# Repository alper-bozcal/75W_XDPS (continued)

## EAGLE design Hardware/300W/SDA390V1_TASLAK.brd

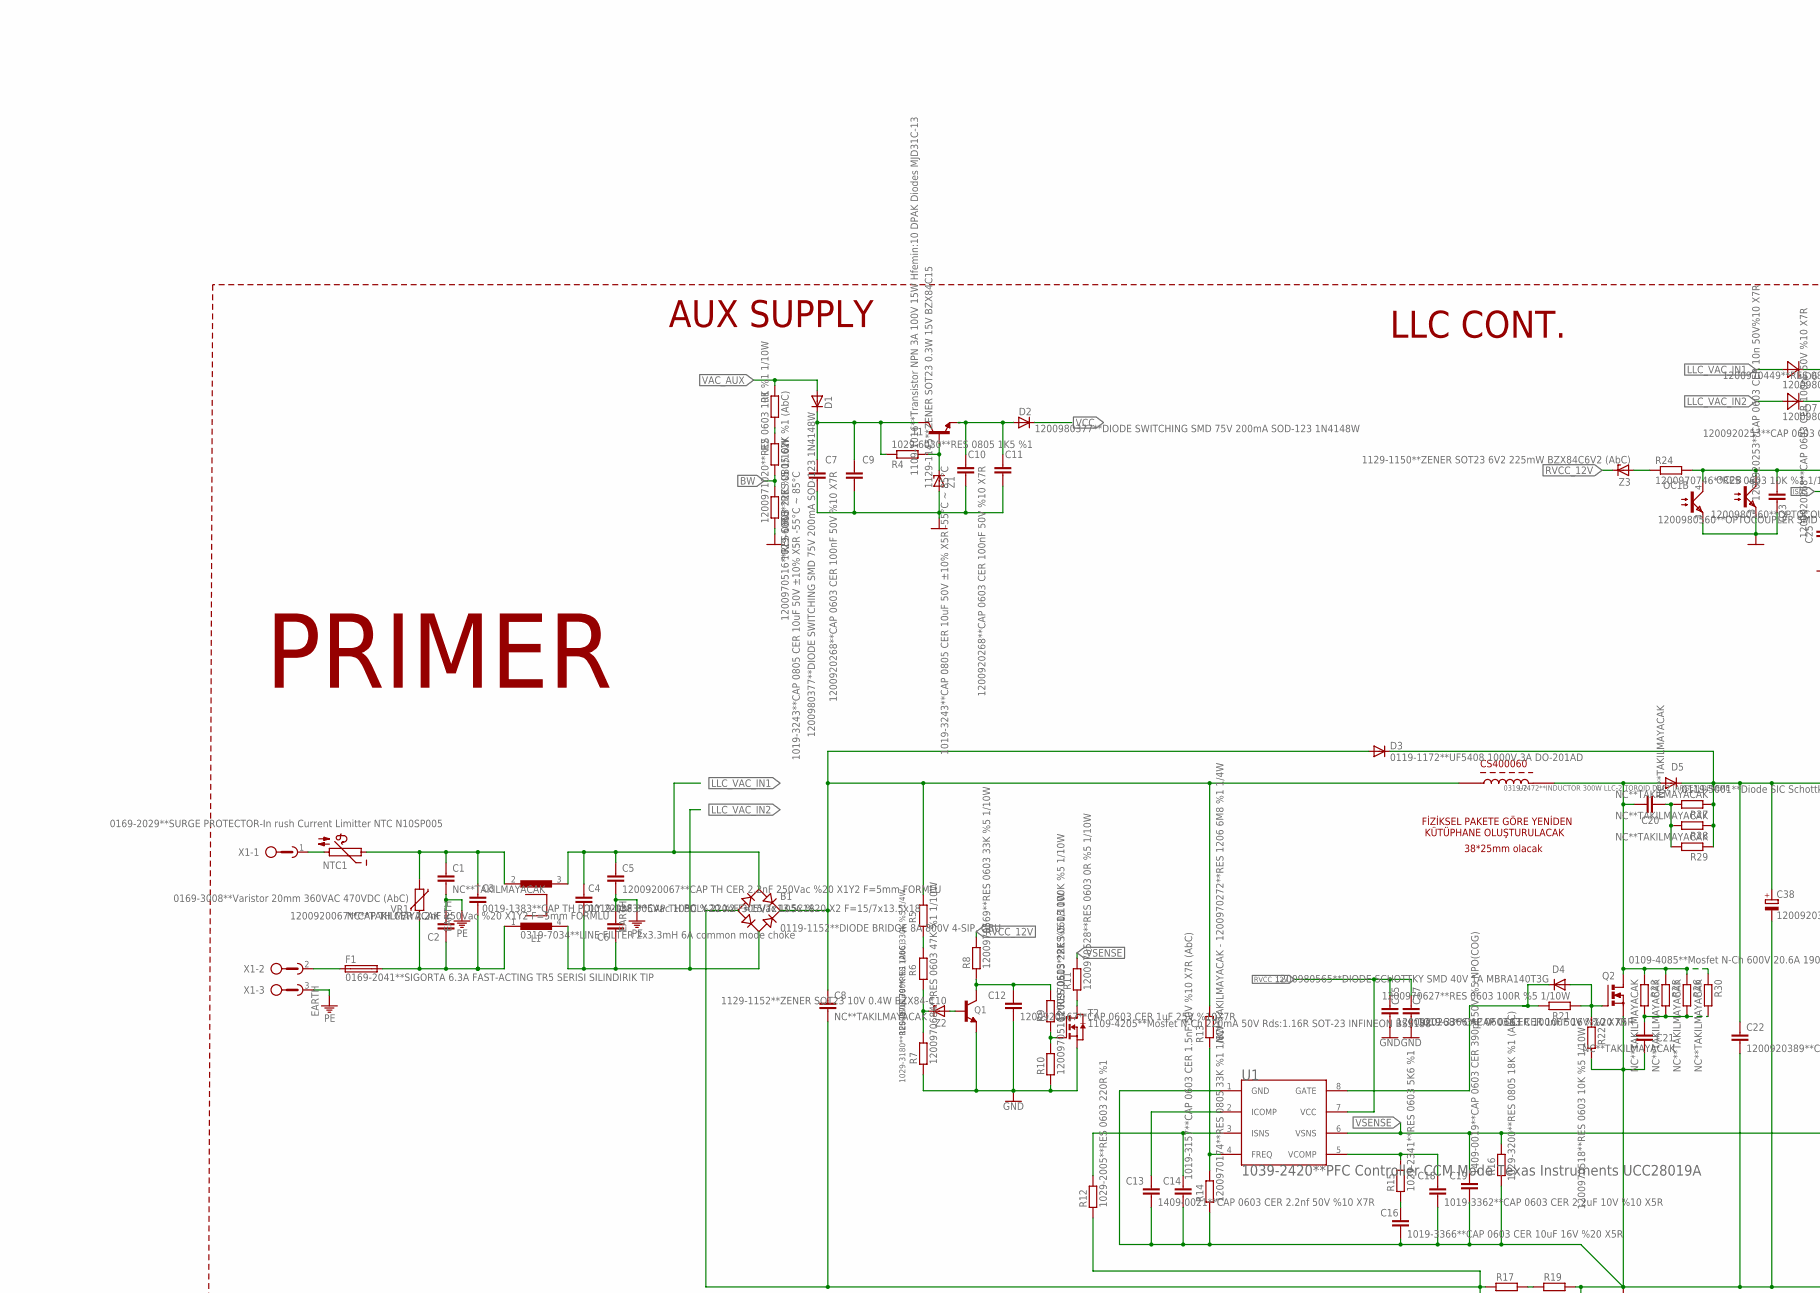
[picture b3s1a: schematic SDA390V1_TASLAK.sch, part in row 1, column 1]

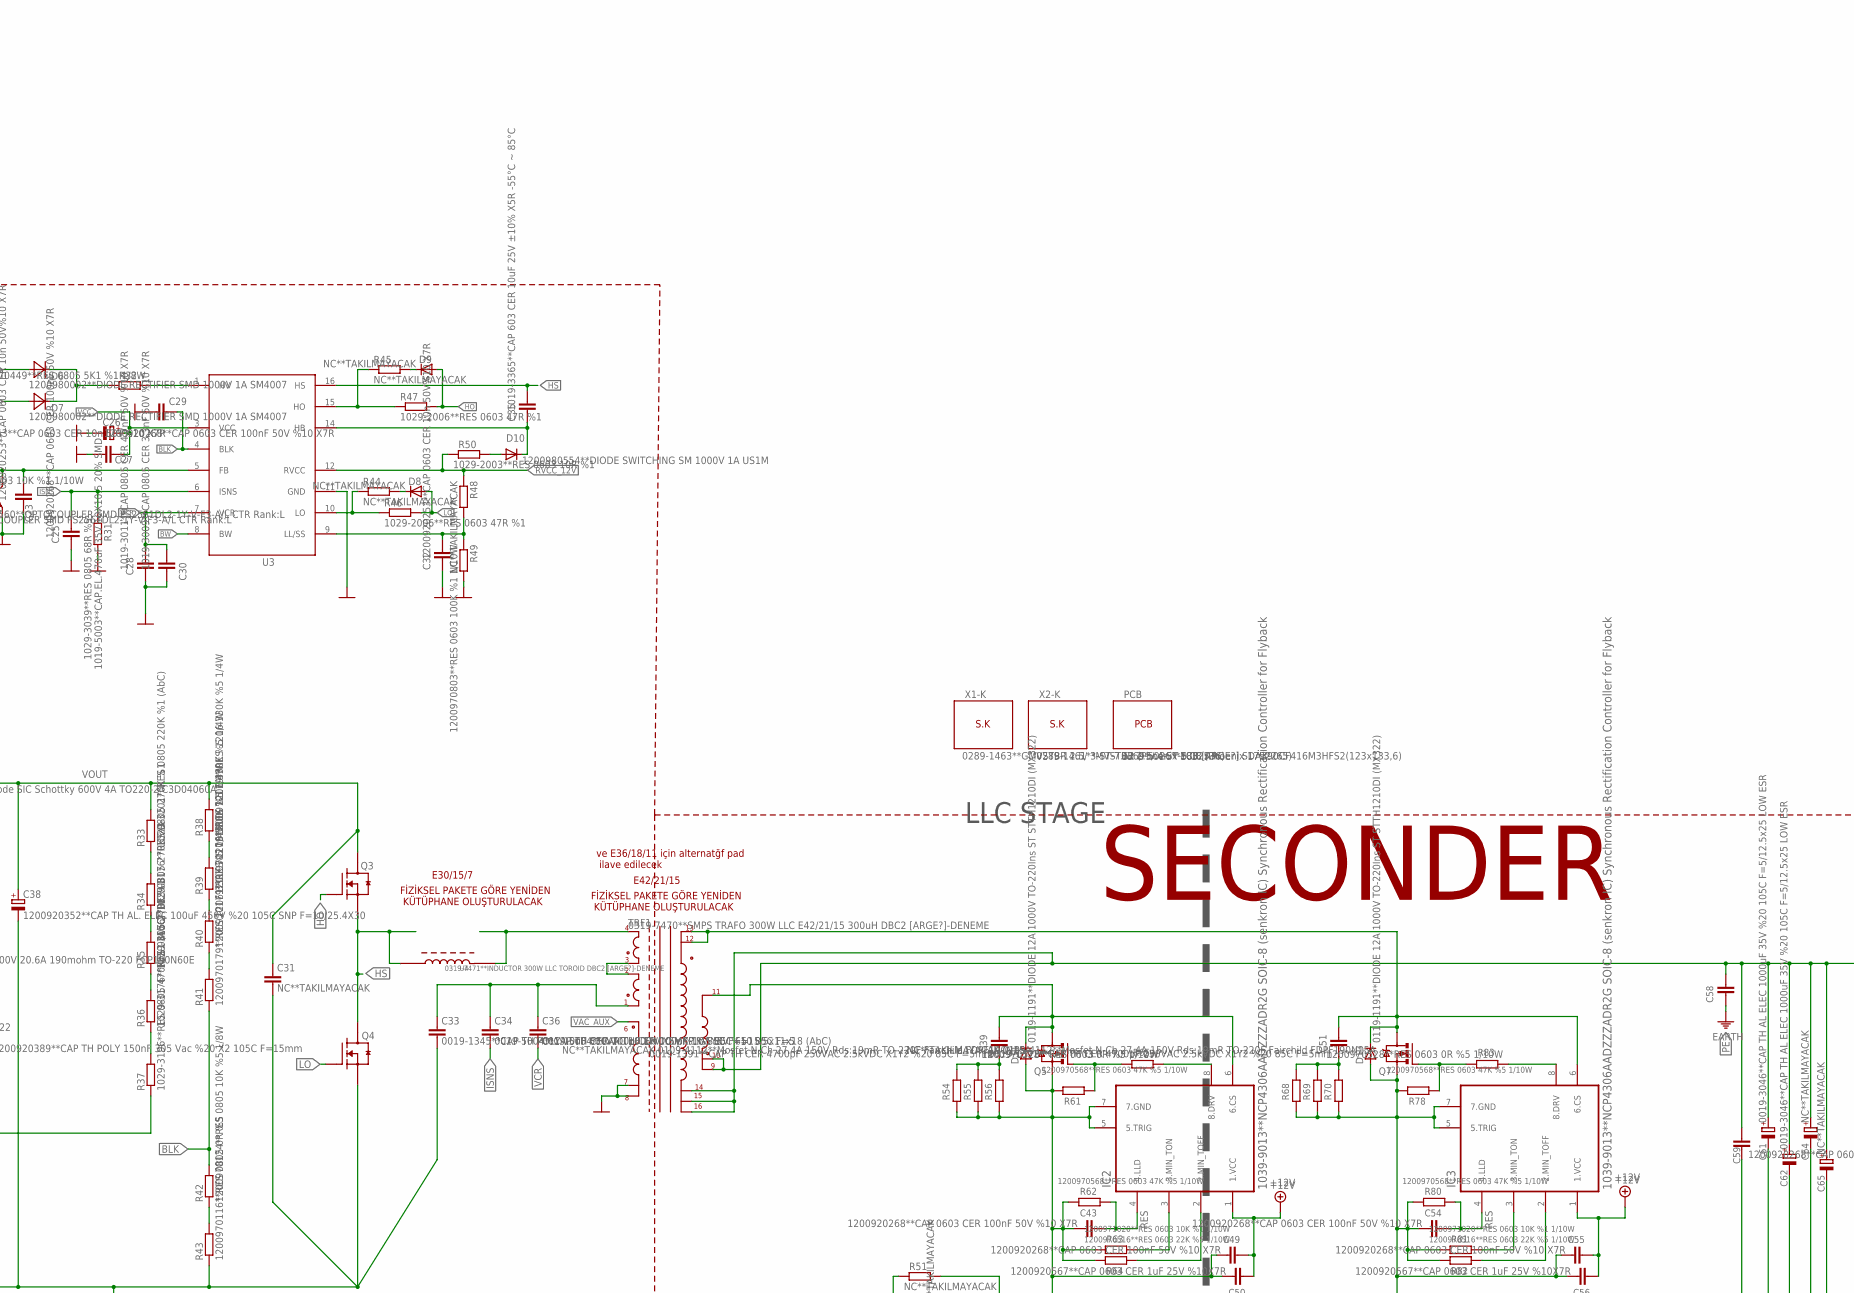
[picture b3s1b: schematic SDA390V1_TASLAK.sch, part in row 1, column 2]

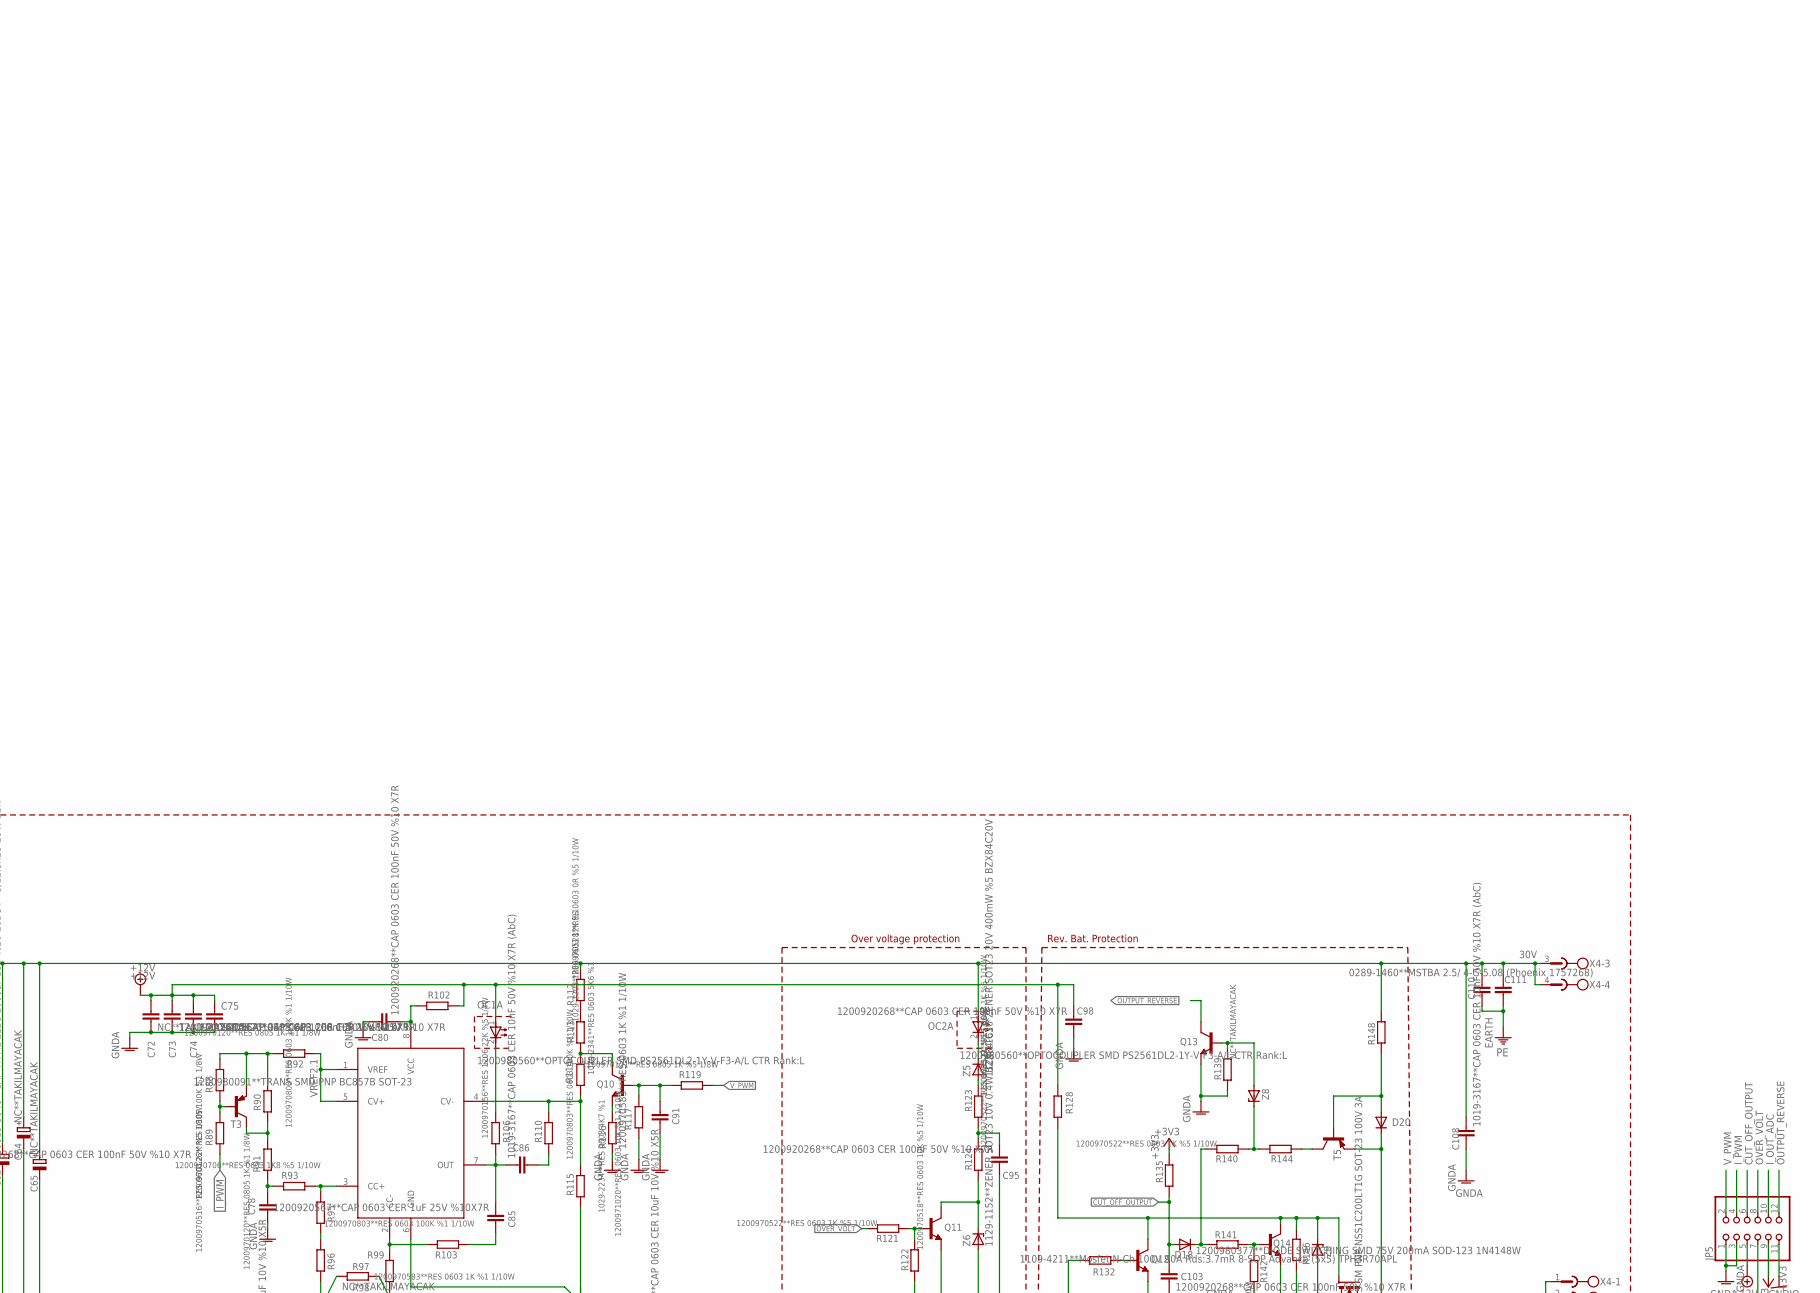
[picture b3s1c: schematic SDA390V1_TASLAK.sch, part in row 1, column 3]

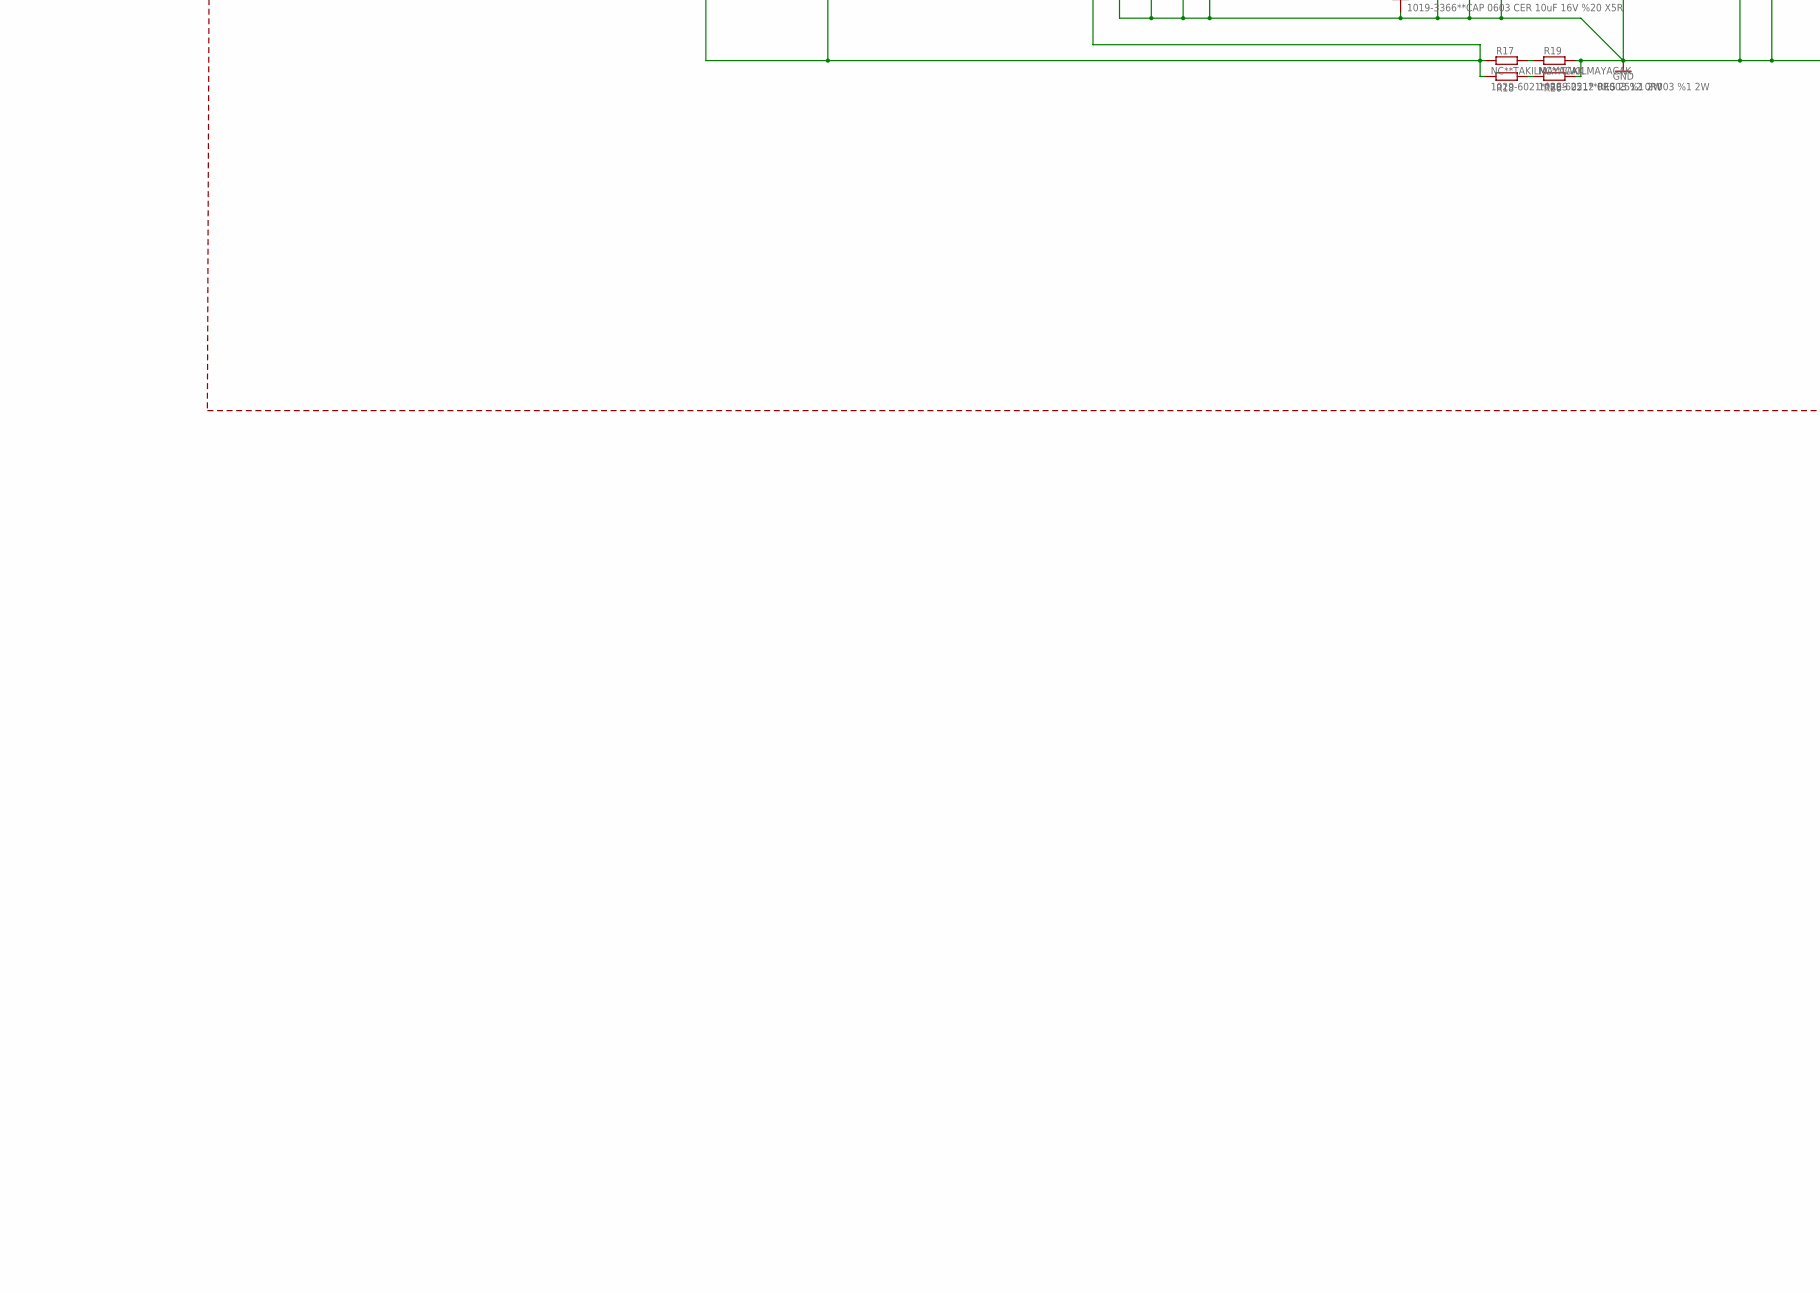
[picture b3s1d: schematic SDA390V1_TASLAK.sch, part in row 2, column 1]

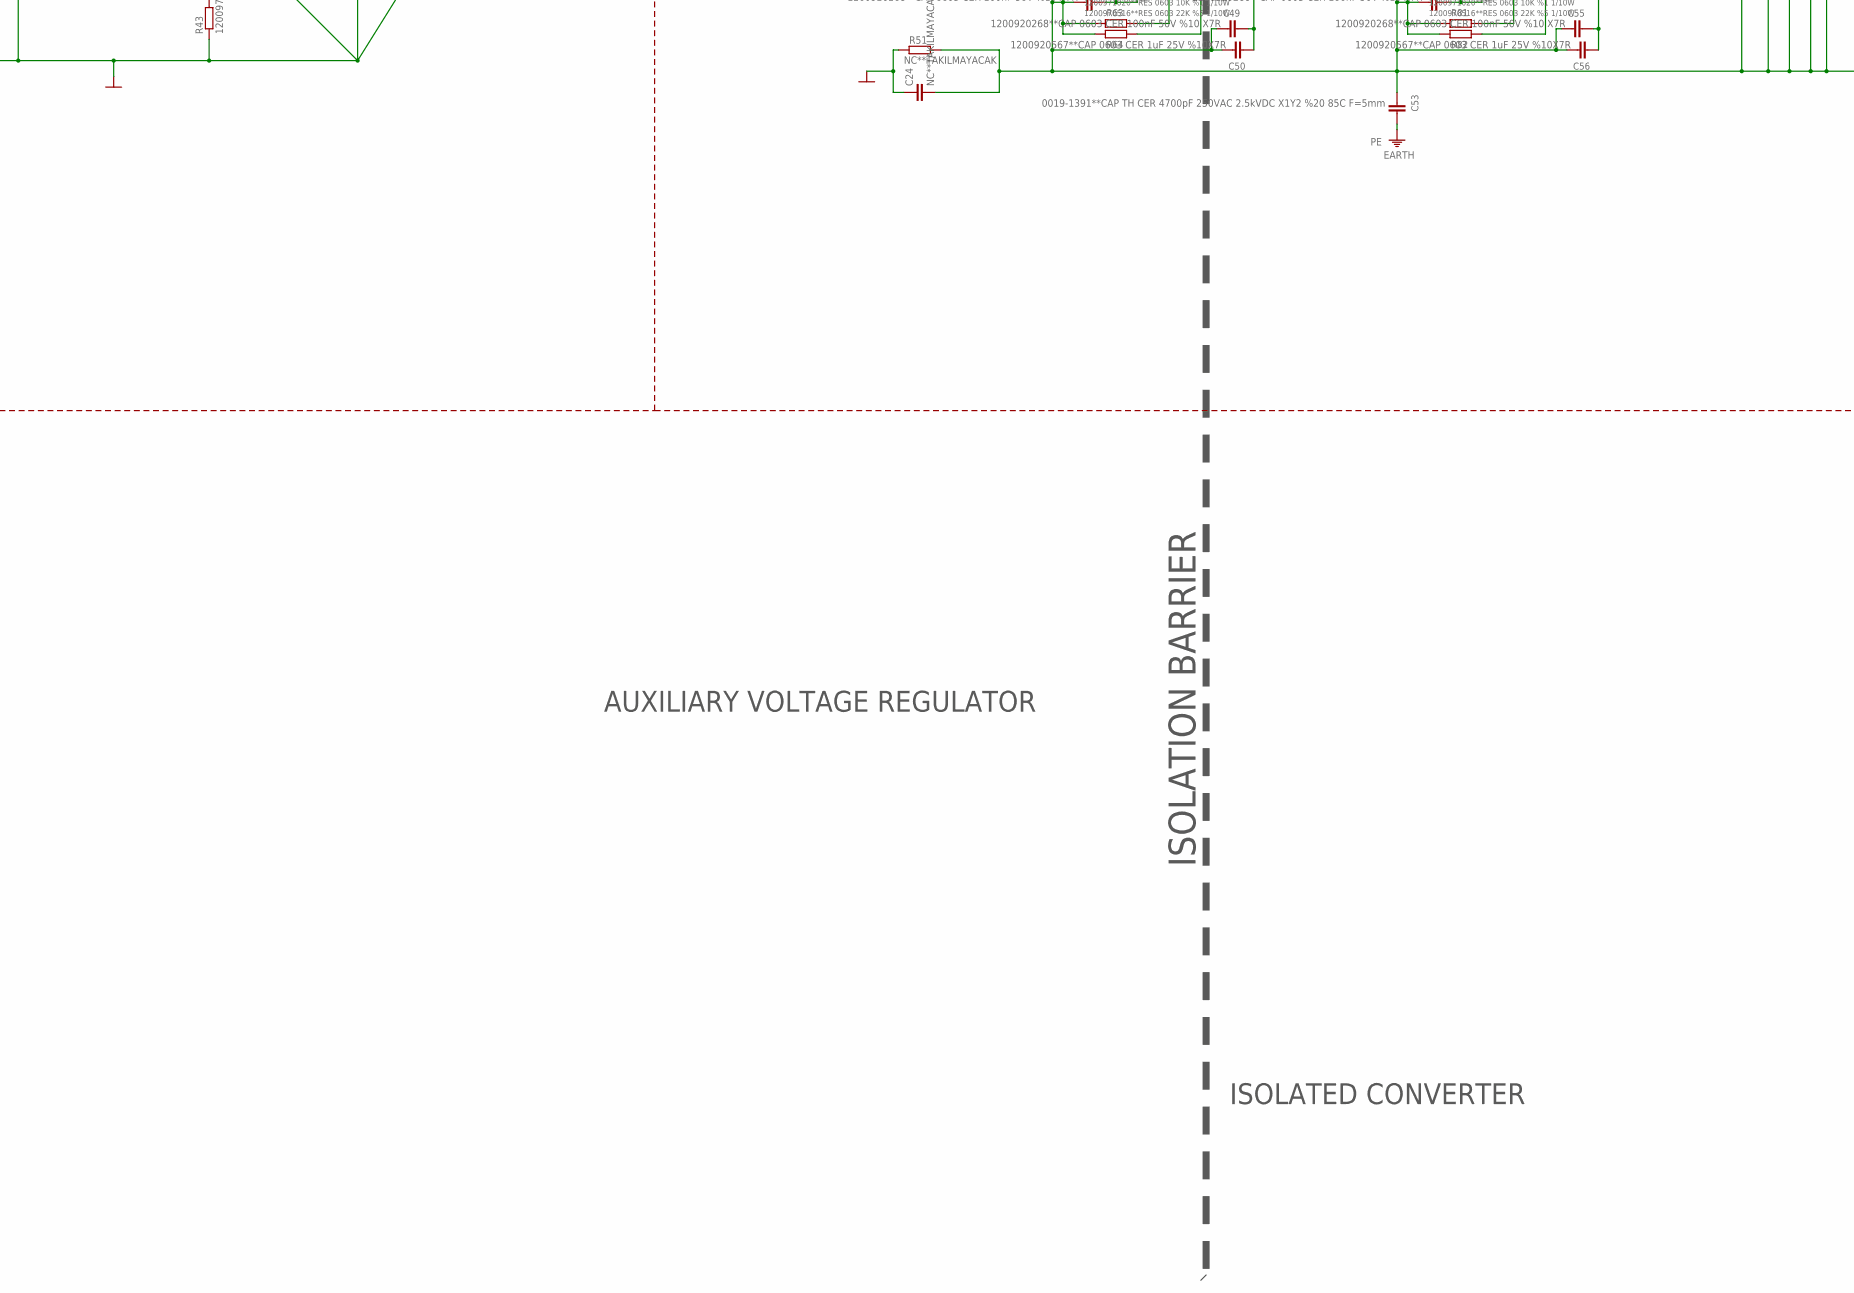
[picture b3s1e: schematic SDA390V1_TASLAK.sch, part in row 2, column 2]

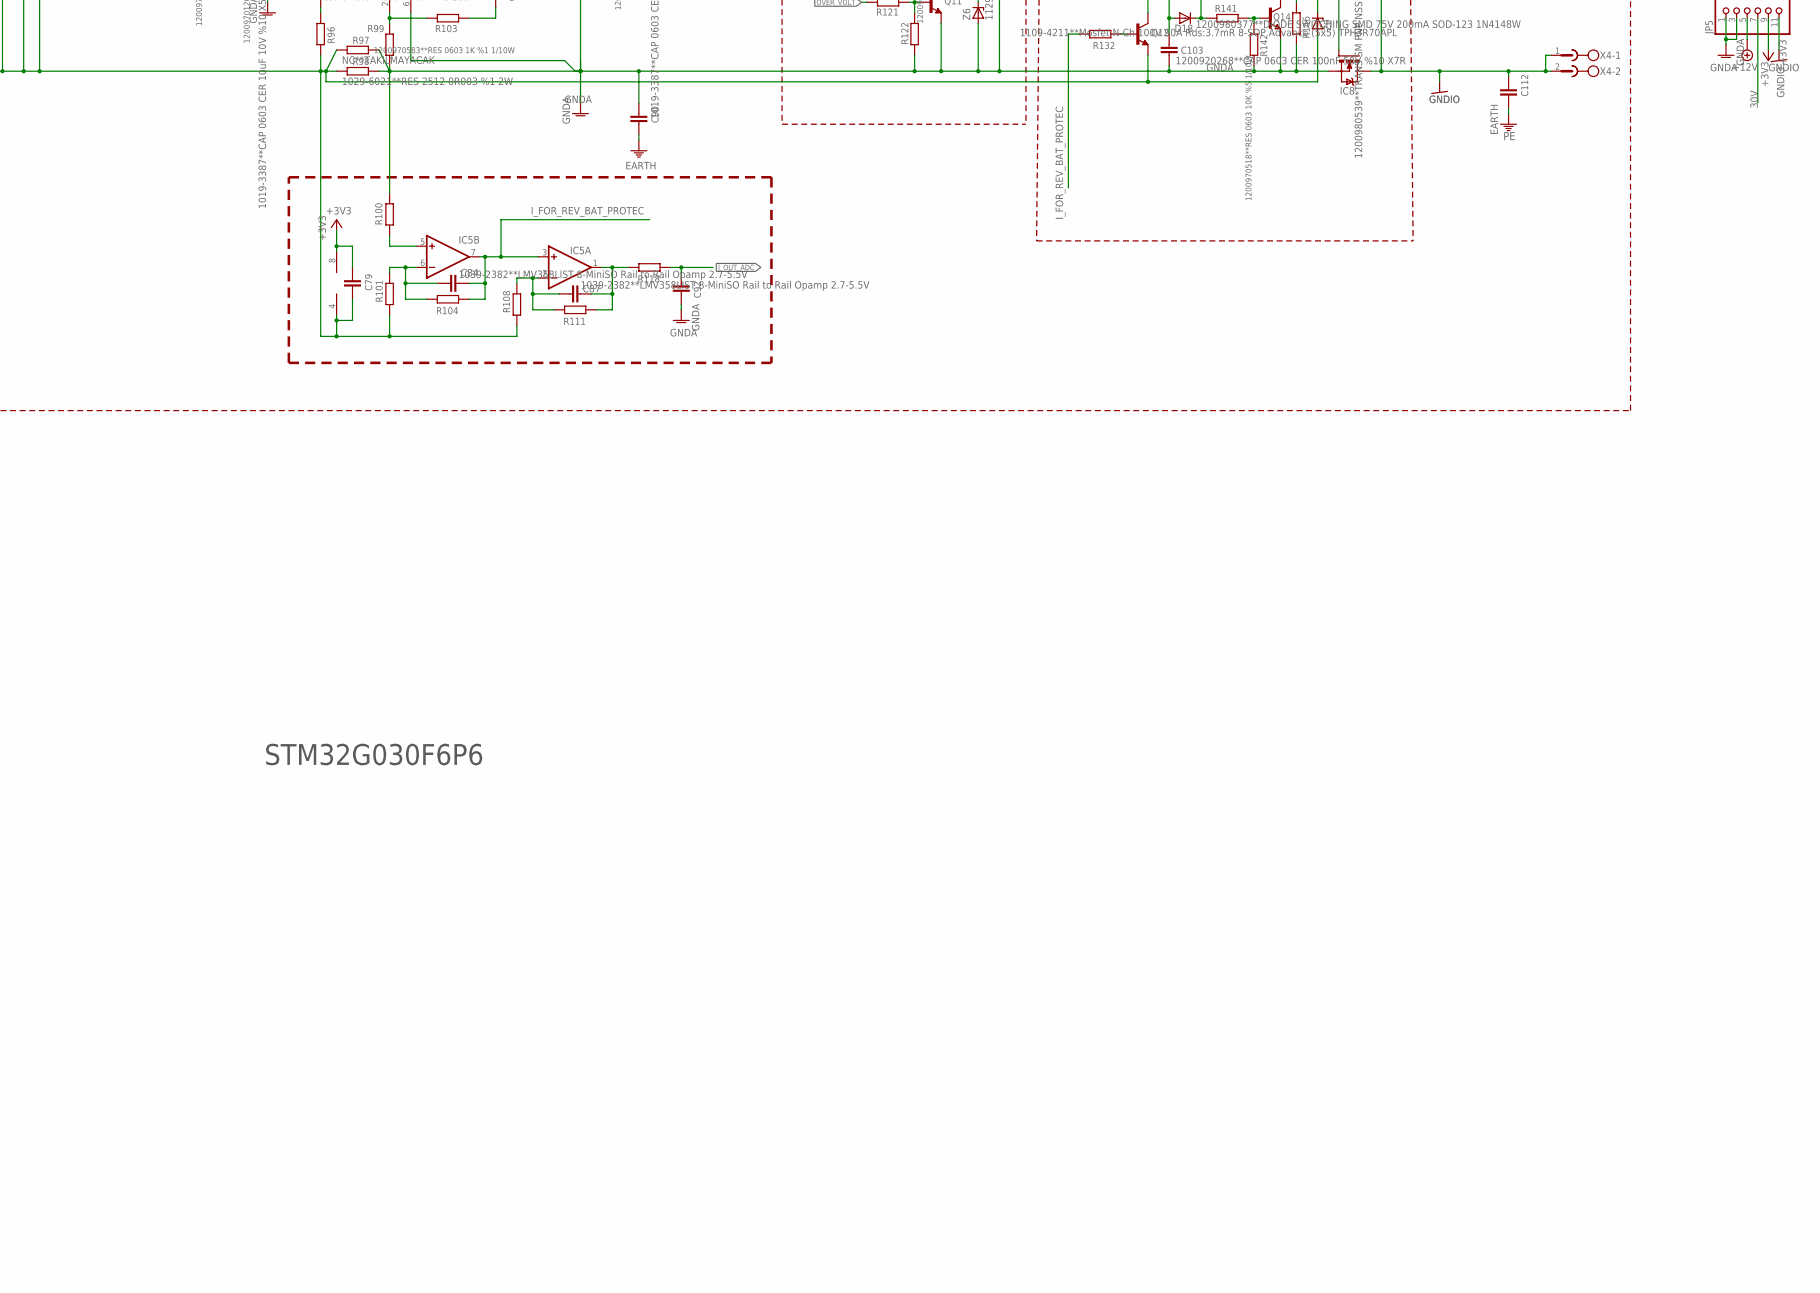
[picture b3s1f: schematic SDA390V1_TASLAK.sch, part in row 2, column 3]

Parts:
B1: 0119-1152**DIODE BRIDGE 8A 800V 4-SIP, GBU; DıODE_BRIDGE_8A_DIK
C1, C2: NC**TAKILMAYACAK; C050-035X075
C3, C4: 0019-1383**CAP TH POLY 220nF 305Vac 105C %20 X2 F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; C150-064X183
C5, C6: 1200920067**CAP TH CER 2.2nF 250Vac %20 X1Y2 F=5m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; C050-035X075
C7, C10: 1019-3243**CAP 0805 CER 10uF 50V ±10% X5R -55°C ~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; C0805_ENKO
C8: NC**TAKILMAYACAK; C225-087X268
C9, C11, C15, C25, C27, C43, C49, C54, C55, C59, C73, C79, C80, C92, C95, C98, C103: 1200920268**CAP 0603 CER 100nF 50V %10 X7R; C0603_ENKO
C12, C50, C56, C74, C85: 1200920567**CAP 0603 CER 1uF 25V %10X7R; C0603_ENKO
C13: 1409-0021**CAP 0603 CER 2.2nf 50V %10 X7R; C0603_ENKO
C14: 1019-3157**CAP 0603 CER 1.5nF 50V %10 X7R (AbC); C0603_ENKO
C16, C17: 1019-3366**CAP 0603 CER 10uF 16V %20 X5R; C0603_ENKO
C18: 1019-3362**CAP 0603 CER 2.2uF 10V %10 X5R; C0603_ENKO
C19: 1409-0019**CAP 0603 CER 390pf 50V %5 NPO(COG); C0603_ENKO
C20, C21: NC**TAKILMAYACAK; C050-030X075
C22: 1200920389**CAP TH POLY 150nF 305 Vac %20 X2 105C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; C150-054X183
C23, C29, C32: 1200920253**CAP 0603 CER 10n 50V%10 X7R; C0603_ENKO
C24: NC**TAKILMAYACAK; C075-32X103_DEIF
C26: 1019-5003**CAP.EL.470uF 35V 10X10.5 20% SMD; 153CLV-1010
C28: 1019-3011**CAP 0805 CER 4.7nF 50V %10 X7R; C0603_ENKO
C30: 1019-3009**CAP 0805 CER 3.3nF 50V %10 X7R; C0603_ENKO
C31: NC**TAKILMAYACAK; C150-064X183
C33: 0019-1345**CAP TH POLY 10nF 600VAC 1000VDC MKP %5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; C150-072X183
C34: 0019-5004**CAP TH CER 100pF 1kV Y5V %10 85C F=5; C050-055X075
C35: 1019-3365**CAP 603 CER 10uF 25V ±10% X5R -55°C ~ 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; C0603_ENKO
C36: 0019-5004**CAP TH CER 100pF 1kV Y5V %10 85C F=5; C050-050X075
C38: 1200920352**CAP TH AL. ELEC 100uF 450V %20 105C S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; EB25D
C39, C51, C53: 0019-1391**CAP TH CER 4700pF 250VAC 2.5kVDC X1Y2 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; C050-045X075
C58: 1200920292**CAP TH CER 2.2nF 300Vac %20 X1Y2 F=7.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; C075-32X103/C050-035X75
C61, C62: 0019-3046**CAP TH AL ELEC 1000uF 35V %20 105C F=5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; E5-13/E7,5-16
C64, C65: NC**TAKILMAYACAK; E5-13/E7,5-16
C72: NC**TAKILMAYACAK; C0603_ENKO
C75: 1200920197**CAP 1206 CER 10uF 25V %10 X7R; C1206_ENKO
C78, C91: 1019-3387**CAP 0603 CER 10uF 10V %10 X5R; C0603_ENKO
C84: NC**TAKILMAYACAK (Not Fitted); C0603_ENKO
C86, C108: 1019-3167**CAP 0603 CER 10nF 50V %10 X7R (AbC); C0603_ENKO
C87: 1200920371**CAP 0603 CER 150p 50V%5 COG; C0603_ENKO
C90: NC**TAKILMAYACAK (Not Fitted); C050-035X075
C110, C111, C112: 0019-1391**CAP TH CER 4700pF 250VAC 2.5kVDC X1Y2 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; C050-035X075
D1, D2, D18, D20: 1200980377**DIODE SWITCHING SMD 75V 200mA SOD-123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; SOD123
D3: 0119-1172**UF5408 1000V 3A DO-201AD; DIODE_D0201-23
D4: 1200980565**DIODE SCHOTTKY SMD 40V 1A MBRA140T3G; SOD106-R
D5: 0119-5001**Diode SIC Schottky 600V 4A TO220-2 C3D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; DIODE_12A_1000V_TO220
D6, D7: 1200980002**DIODE RECTIFIER SMD 1000V 1A SM4007; M7_DC_DIYOT
D8, D9: NC**TAKILMAYACAK; SOD106-R
D10: 1200980554**DIODE SWITCHING SM 1000V 1A US1M; SOD106-R
D11, D13: 0119-1191**DIODE 12A 1000V TO-220Ins ST STTH1210D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; TO220ACS
F1: 0169-2041**SIGORTA 6.3A FAST-ACTING TR5 SERISI SI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; 19560
IC2, IC3: 1039-9013**NCP4306AADZZZADR2G SOIC-8 (senkron IC)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; NCP4306
IC4: 1039-2224**TSM1011ID SO-8 Constant Voltage and Co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; SO-8
IC5: 1039-2382**LMV358LIST 8-MiniSO Rail to Rail Opamp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; MSOP08
IC8: 1109-4211**Mosfet N-Ch 100V 90A Rds:3.7mR 8-SOP A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; TPH6R30ANL
JP5: PINHD-2X6_2.54; 2X06
L1: 0319-7034**LINE FILTER 2x3.3mH 6A common mode cho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; EPCOS_B82724J
NTC1: 0169-2029**SURGE PROTECTOR-In rush Current Limitt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; SENS_NTC
OC1, OC2: 1200980560**OPTOCOUPLER SMD PS2561DL2-1Y-V-F3-A/L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; PS2561DL2-1_OPTO1
PCB: 0369-5026**PCB [ARGE?] SDA390CF416M3HFS2(123x133,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; PCB
Q1, Q10, Q11, Q12, Q14: 1200980090**TRANS SMD NPN BC847B SOT-23; SOT23
Q2: 0109-4085**Mosfet N-Ch 600V 20.6A 190mohm TO-220 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; TO220BV
Q3, Q4: 0109-4091**Mosfet N-Ch 800V 9A 0.16R TO-220FP Vis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; ISO_TO_220
Q5, Q7: NC**TAKILMAYACAK 0109-4112**Mosfet N-Ch 27.4A 150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; TO220BV
Q13: NC**TAKILMAYACAK; SOT23
R1: 1029-6060**RES 0805 62K %1 (AbC); R0603_ENKO
R2, R10, R64, R82, R89, R135: 1200970516**RES 0603 22K %5 1/10W; R0603_ENKO
R3, R63, R81, R117: 1200971020**RES 0603 10K %1 1/10W; R0603_ENKO
R4: 1029-6030**RES 0805 1K5 %1; R0805_ENKO
R5, R38, R39, R40, R41: 1200970179**RES 1206 330K %5 1/4W; R1206_ENKO
R6: 1029-3180**RES 0805 300K %1 (AbC); R1206_ENKO
R7: 1200970684**RES 0603 47K %1 1/10W; R0603_ENKO
R8: 1200970569**RES 0603 33K %5 1/10W; R0603_ENKO
R9, R128: 1200970515**RES 0603 100K %5 1/10W; R0603_ENKO
R11, R65, R83, R112: 1200970528**RES 0603 0R %5 1/10W; R0603_ENKO
R12: 1029-2005**RES 0603 220R %1; R0603_ENKO
R13: NC**TAKILMAYACAK - 1200970272**RES 1206 6M8 %1 1/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; R1206_ENKO
R14: 1200970174**RES 0805 33K %1 1/8W; R0805_ENKO
R15, R114: 1029-2341**RES 0603 5K6 %1; R0603_ENKO
R16: 1029-3200**RES 0805 18K %1 (AbC); R0805_ENKO
R17, R19, R97: NC**TAKILMAYACAK; R2512
R18, R20, R98: 1029-6021**RES 2512 0R003 %1 2W; R2512
R21: 1200970627**RES 0603 100R %5 1/10W; R0603_ENKO
R22, R122, R142: 1200970518**RES 0603 10K %5 1/10W; R0603_ENKO
R23, R25, R26, R27, R28, R29, R30, R55, R69: NC**TAKILMAYACAK; R1206_ENKO
R24: 1200970746**RES 0603 10K %1 1/10W; R0603_ENKO
R31: 1029-3039**RES 0805 68R %5; R0603_ENKO
R32: 1200970449**RES 0805 5K1 %1 1/8W; R0805_ENKO
R33: 1029-3201**RES 0805 220K %1 (AbC); R0805_ENKO
R34, R35, R36: 1029-3176**RES 0805 270K %1; R0805_ENKO
R37: 1029-3196**RES 0805 470K %1 (AbC); R0805_ENKO
R42: 1200970124**RES 0805 10K %5 1/8W; R0805_ENKO
R43: 1200970116**RES 0805 0R %5; R0805_ENKO
R44, R45, R48, R139: NC**TAKILMAYACAK; R0603_ENKO
R46, R47: 1029-2006**RES 0603 47R %1; R0603_ENKO
R49, R90, R103, R110: 1200970803**RES 0603 100K %1 1/10W; R0603_ENKO
R50, R95, R102: 1029-2003**RES 0603 10R %1; R0603_ENKO
R51: NC**TAKILMAYACAK; 0207/15
R54, R56, R68, R70: 1029-4045**RES 1206 22R %5; R1206_ENKO
R61, R62, R78, R80: 1200970568**RES 0603 47K %5 1/10W; R0603_ENKO
R88: 1200970126**RES 0805 100K %1 1/8W; R0805_ENKO
R91, R92: 1200970120**RES 0805 1K %1 1/8W; R0805_ENKO
R93: 1200970706**RES 0603 1K8 %5 1/10W; R0603_ENKO
R96: 1029-3416**RES 0805 47R %1 (AbC) (MX322); R0805_ENKO
R99, R108, R116: 1200970583**RES 0603 1K %1 1/10W; R0603_ENKO
R100, R101, R118, R121, R123, R124, R132, R140, R141: 1200970522**RES 0603 1K %5 1/10W; R0603_ENKO
R104, R115: 1029-2234**RES 0603 4K7 %1; R0603_ENKO
R106: 1200970156**RES 1206 22K %5 1/4W; R1206_ENKO
R111: 1029-6089**RES 0603 6K8 %5; R0603_ENKO
R113: 1029-2203**RES 0603 12K %1; R0603_ENKO
R119: 1200970121**RES 0805 1K %5 1/8W; R0805_ENKO
R144: 1029-2337**RES 0603 39K %1; R0603_ENKO
R146: 1200970585**RES 0603 1M %5 1/10W; R0603_ENKO
R148: 1029-6015**RES 1206 56K %5; R1206_ENKO
T1: 1109-1016**Transistor NPN 3A 100V 15W Hfemin:10 D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; DPAK
T2: 1109-4205**Mosfet N-Ch 220mA 50V Rds:1.16R SOT-23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; SOT-23
T3: 1200980091**TRANS SMD PNP BC857B SOT-23; SOT23-BEC
T5: 1200980539**TRANS SM PNP NSS1C200LT1G SOT-23 100V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; SOT23-BEC
TRF1: 0319-7470**SMPS TRAFO 300W LLC E42/21/15 300uH DB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; DEIF_TRF_300W_2
U1: 1039-2420**PFC Controller CCM Mode Texas Instrume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; UCC28180
U2: 0319-7472**INDUCTOR 300W LLC-2 TOROID DBC2 [ARGE?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; IND_TOROID
U3: 1039-2421**LLC Controller Texas Instruments UCC25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; SOIC16_UCC256301
U4: 0319-7471**INDUCTOR 300W LLC TOROID DBC2 [ARGE?]-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; IND_TOROID
VR1: 0169-3008**Varistor 20mm 360VAC 470VDC (AbC); VITRA_VARISTOR
X1: 0289-1462**GMSTBA 2.5/ 3-G-7.62 (Phoenix 1766246); GMSTBA3
X1-K: 0289-1463**GMVSTBR 2.5/ 3-ST-7.62 (Phoenix 183253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; SOKET
X2-K: 0289-1461**MVSTBR 2.5/ 4-ST-5.08 (Phoenix 1792265); SOKET
X4: 0289-1460**MSTBA 2.5/ 4-G-5.08 (Phoenix 1757268); MSTBA4
Z1: 1129-1145**ZENER SOT23 0.3W 15V BZX84C15; SOT23
Z2, Z6: 1129-1152**ZENER SOT23 10V 0.4W BZX84-C10; SOT23
Z3, Z9: 1129-1150**ZENER SOT23 6V2 225mW BZX84C6V2 (AbC); SOT23
Z5: 1129-1163**ZENER SOT23 20V 400mW %5 BZX84C20V; SOT23
Z8: NC**TAKILMAYACAK; SOT23

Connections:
30V: C58.1, C58.3 (1), C59.1, C61.+, C61.+1 (+), C62.+, C62.+1 (+), C64.+, C64.+1 (+), C65.+, C65.+1 (+), C108.2, C110.1, C111.1, JP5.7, OC2.1, R112.2, R148.1, TRF1.6.1 (9), TRF1.6.2 (9), TRF1.6.5 (9), TRF1.7 (10), TRF1.11 (14), TRF1.12 (15), TRF1.13 (16), TRF1.19 (15), TRF1.20 (14), TRF1.24 (10), TRF1.25 (16), TRF1.27 (10), TRF1.31 (14), TRF1.32 (15), TRF1.38 (16), TRF1.40 (9), TRF1.41 (10), TRF1.45 (14), TRF1.46 (15), TRF1.47 (16), X4.3, X4.4
+3V3: C79.1, IC5.8 (V+), JP5.9, R135.2
+12V: C49.2, C50.2, C55.2, C56.2, C72.1, C73.1, C74.1, C75.1, C98.2, IC2.1 (1.VCC), IC3.1 (1.VCC), JP5.5, OC1.1, R102.1, R128.2
BLK: C29.2, R41.1, R42.2, U3.4 (BLK)
BW: R2.2, R3.2, U3.8 (BW)
CUT_OFF_OUTPUT: C103.1, D18.A, JP5.6, R135.1
GATE1: IC8.GATE (G4), Q12.3 (C), Q14.3 (C), R128.1, R146.2, Z9.3 (C)
GND: C7.1, C9.1, C10.1, C11.1, C12.2, C13.2, C14.2, C15.2, C16.2, C17.2, C18.2, C19.2, C21.1, C22.2, C23.2, C24.P$1 (1), C25.2, C26.-, C27.2, C28.2, C29.1, C30.2, C31.2, C32.2, C33.2, C38.-, OC1.3, OC2.3, Q1.2 (E), Q2.S, Q4.3 (S), R3.1, R7.1, R10.1, R14.1, R16.1, R19.2, R20.2, R22.2, R31.2, R43.1, R49.2, R51.1, T2.2 (S), TRF1.4 (8), TRF1.6 (7), TRF1.14 (7), TRF1.26 (8), TRF1.33 (7), TRF1.39 (8), TRF1.48 (8), TRF1.49 (7), U1.1 (GND), U3.11 (GND), Z1.1 (A)
GNDA: C72.2, C73.2, C74.2, C75.2, C78.1, C80.1, C90.2, C91.1, C92.1, C95.1, C98.1, C103.2, C108.1, IC4.6 (GND), IC8.S (S123), IC8.S1 (S123), IC8.S2 (S123), JP5.1, JP5.3, Q11.2 (E), Q13.2 (E), Q14.2 (E), R97.2, R98.2, R99.2, R100.2, R115.1, R116.1, R117.2, R122.1, R139.1, R142.2, R146.1, Z6.1 (A)
GNDIO: C112.2, D20.C, IC8.D (D5678), IC8.D1 (D5678), IC8.D2 (D5678), IC8.D3 (D5678), IC8.P$1 (D5678), IC8.P$2 (D5678), JP5.11, T5.E, X4.1, X4.2
HO: D9.A, Q3.1 (G), R47.2
HS: C35.1, Q3.3 (S), Q4.2 (D), U3.16 (HS), U4.1
ISNS: C25.1, C34.2, R31.1, U3.6 (ISNS)
I_FOR_REV_BAT_PROTEC: C84.2, IC5.3 (+IN), IC5.7 (OUT), R104.2, R132.2
I_OUT_ADC: C92.2, JP5.10, R118.2
I_PWM: JP5.4, R89.2
LLC_VAC_IN1: B1.AC1, C4.1, C5.1, D6.A, L1.3
LLC_VAC_IN2: B1.AC2, C4.2, C6.1, D7.A, L1.4
LO: D8.A, Q4.1 (G), R46.2
unnamed: R4.2, T1.1 (B), Z1.3 (C)
unnamed: R1.2, R2.1
unnamed: R39.1, R40.2
unnamed: R112.1, R113.2
unnamed: R95.1, R96.2
unnamed: F1.1, X1.2
unnamed: R24.1, Z3.1 (A)
unnamed: C85.2, C86.2, IC4.7 (OUT), R106.1
unnamed: C78.2, R91.2, R93.2
unnamed: R32.1, U3.1 (HV)
unnamed: R5.2, R6.1
unnamed: C35.2, D10.C, U3.14 (HB)
unnamed: IC4.3 (CC+), R93.1, R95.2
unnamed: R88.2, R89.1, T3.B
unnamed: Q10.3 (C), R113.1, R114.2
unnamed: IC4.4 (CV-), R110.2, R114.1, R115.2
unnamed: C32.1, R48.2, R49.1, U3.9 (LL/SS)
unnamed: IC4.2 (CC-), R99.1, R103.2
unnamed: C91.2, Q10.1 (B), R117.1, R119.2
unnamed: D6.C, D7.C, R32.2
unnamed: R123.2, Z5.1 (A)
unnamed: C95.2, R123.1, R124.2
unnamed: Q11.1 (B), R121.1, R122.2
unnamed: C7.2, C9.2, D1.C, R4.1, T1.4 (C)
unnamed: OC2.2, Z5.3 (C)
unnamed: Q12.1 (B), R132.1
unnamed: C87.2, IC5.1 (OUT), R111.2, R118.1
unnamed: C80.2, IC4.8 (VCC), R102.2
unnamed: C84.1, IC5.6 (-IN), R101.2, R104.1
unnamed: IC5.5 (+IN), R100.1
unnamed: C87.1, IC5.2 (-IN), R108.2, R111.1
unnamed: R40.1, R41.2
unnamed: R42.1, R43.2
unnamed: R38.1, R39.2
unnamed: D18.C, R140.2, R141.2
unnamed: C86.1, R110.1
unnamed: Q13.1 (B), R139.2, Z8.1 (A)
unnamed: TRF1.3 (4), TRF1.16 (4), TRF1.35 (4), TRF1.52 (4), U4.2
unnamed: Q10.2 (E), R116.2
unnamed: D10.A, R50.2
unnamed: C23.1, OC1.4, OC2.4, R24.2, U3.5 (FB)
unnamed: R45.1, R47.1, U3.15 (HO)
unnamed: R44.1, R46.1, U3.10 (LO)
unnamed: C33.1, C34.1, C36.1, TRF1.55 (1), TRF1.56 (1), TRF1.57 (1), TRF1.58 (1)
unnamed: R88.1, R90.2, R92.2, T3.E
unnamed: C14.1, R12.2, U1.3 (ISNS)
unnamed: R11.1, T2.1 (D)
unnamed: D4.A, Q2.G, R21.1, R22.1
unnamed: R13.1, R14.2, U1.4 (FREQ)
unnamed: C12.1, Q1.3 (C), R8.1, R9.2
unnamed: Q11.3 (C), R124.1, Z6.3 (C)
unnamed: TRF1.1 (2), TRF1.2 (3), TRF1.17 (3), TRF1.18 (2), TRF1.36 (3), TRF1.37 (2), TRF1.53 (3), TRF1.54 (2)
unnamed: C1.1, C3.1, L1.2, NTC1.P$1 (1), VR1.1
unnamed: C20.1, D5.A, Q2.D, R23.1, R25.1, R26.1, R30.1, U2.2
unnamed: R6.2, R7.2, Z2.3 (C)
unnamed: C16.1, R15.1
unnamed: C13.1, U1.2 (ICOMP)
unnamed: D9.C, R45.2
unnamed: Q5.G, R61.1, R65.2
unnamed: C20.2, R27.2, R28.2, R29.2
unnamed: C21.2, R23.2, R25.2, R26.2, R30.2
unnamed: IC2.2 (2.MIN_TOFF), R64.1
unnamed: D8.C, R44.2
unnamed: B1.+, C8.1, D3.A, R5.1, R13.2, U2.1
unnamed: R140.1, R144.1, Z8.3 (C)
unnamed: NTC1.P$2 (2), X1.1
unnamed: C18.1, R15.2, U1.5 (VCOMP)
unnamed: R90.1, R91.1, T3.C
unnamed: D20.A, R148.2, T5.B
unnamed: R33.1, R34.2
unnamed: R34.1, R35.2
unnamed: R35.1, R36.2
unnamed: R36.1, R37.2
unnamed: R144.2, T5.C
unnamed: IC2.3 (3.MIN_TON), R63.1
unnamed: Q14.1 (B), R141.1, R142.1
unnamed: IC2.8 (8.DRV), R65.1
unnamed: C39.2, R54.1, R55.1, R56.1
unnamed: C39.1, D11.C, IC2.6 (6.CS), Q5.D, TRF1.8 (11), TRF1.23 (11), TRF1.28 (11), TRF1.42 (11)
unnamed: R9.1, R10.2, T2.3 (G)
unnamed: Q1.1 (B), Z2.1 (A)
unnamed: B1.-, C8.2, R12.1, R17.1, R18.1
unnamed: Q7.G, R78.1, R83.2
unnamed: IC3.2 (2.MIN_TOFF), R82.1
unnamed: IC3.3 (3.MIN_TON), R81.1
unnamed: IC3.8 (8.DRV), R83.1
unnamed: C51.2, R68.1, R69.1, R70.1
unnamed: R18.2, R20.1
unnamed: R17.2, R19.1
unnamed: C51.1, D13.C, IC3.6 (6.CS), Q7.D, TRF1.9 (12), TRF1.10 (13), TRF1.21 (13), TRF1.22 (12), TRF1.29 (12), TRF1.30 (13), TRF1.43 (12), TRF1.44 (13)
unnamed: C85.1, R103.1
NEUTRAL: C2.1, C3.2, F1.2, L1.1, VR1.2
OUTPUT_REVERSE: JP5.12, Q13.3 (C)
OVER_VOLT: JP5.8, R121.2
PE: C1.2, C2.2, C5.2, C6.2, C53.2, C58.2, C58.4 (2), C90.1, C110.2, C111.2, C112.1, X1.3
Q1_GATE: D4.C, R21.2, U1.8 (GATE)
RES: C43.2, C54.2, IC2.4 (4.LLD), IC3.4 (4.LLD), R62.1, R80.1
RVCC_12V: C15.1, C17.1, R8.2, R48.1, R50.1, U1.7 (VCC), U3.12 (RVCC), Z3.3 (C)
S3: C24.P$2 (2), C43.1, C49.1, C50.1, C53.1, C54.1, C55.1, C56.1, C59.2, C61.-, C61.-1 (-), C62.-, C62.-1 (-), C64.-, C64.-1 (-), C65.-, C65.-1 (-), C79.2, D11.A, D13.A, IC2.5 (5.TRIG), IC2.7 (7.GND), IC3.5 (5.TRIG), IC3.7 (7.GND), IC5.4 (V-), Q5.S, Q7.S, Q12.2 (E), R51.2, R54.2, R55.2, R56.2, R61.2, R62.2, R63.2, R64.2, R68.2, R69.2, R70.2, R78.2, R80.2, R81.2, R82.2, R96.1, R97.1, R98.1, R101.1, R108.1, Z9.1 (A)
U3-K: OC1.2, R106.2
VAC_AUX: D1.A, R1.1, TRF1.5 (6), TRF1.15 (6), TRF1.34 (6), TRF1.50 (6)
VCC: C26.+, C27.1, D2.C, U3.3 (VCC)
VCR: C28.1, C30.1, C36.2, U3.7 (VCR)
VDC_AUX: C10.2, C11.2, D2.A, T1.3 (E)
VOUT: C22.1, C31.1, C38.+, D3.C, D5.K (C), Q3.2 (D), R27.1, R28.1, R29.1, R33.2, R38.2
VREF2.1: IC4.1 (VREF), IC4.5 (CV+), R92.1
VSENSE: C19.1, R11.2, R16.2, R37.1, U1.6 (VSNS)
V_PWM: JP5.2, R119.1

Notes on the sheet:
LLC STAGE
AUXILIARY VOLTAGE REGULATOR
STM32G030F6P6
ISOLATION BARRIER
ISOLATED CONVERTER
FİZİKSEL PAKETE GÖRE YENİDEN KÜTÜPHANE OLUŞTURULACAK
Rev. Bat. Protection
Over voltage protection
E30/15/7
E42/21/15
CS400060
ve E36/18/11 için alternatğf pad ilave edilecek
PRIMER
SECONDER
LLC CONT.
AUX SUPPLY
38*25mm olacak
